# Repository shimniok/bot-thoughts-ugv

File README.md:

This is the repository of electronics and software for Data Bus and Troubled Child, my autonomous ground vehicles. 

* [Troubled Child](http://www.bot-thoughts.com/2014/06/avc-sharc-fsv.html) is a 1986 Jeep Grand Wagoneer that took 1st place in the 2014 Sparkfun AVC.
* [Data Bus](http://www.bot-thoughts.com/p/robot-mag-data-bus.html) is a 1:10 scale RC car that took 3rd place in the 2012 Sparkfun AVC.

The repository contains source code, schematics, board layouts, and documentation. Mostly this is a catch-all for what I worked on in 2010-2014.

* [Current Software](https://github.com/shimniok/diyrovers) - updated versions of the mbed software that handles pose estimation, navigation, and path following
* ```Software/``` - *older* mbed software that handles pose estimation, navigation, path following
* ```Documentation/``` - various supporting documents
* ```Hardware/``` - various hardware used in building and calibrating
* ```Electronics/``` - catch-all of circuit/layout designs varying from experiment to tried and tossed

Some of the electronics are now products on [Tindie.com](https://www.tindie.com/stores/bot_thoughts/) and they have their own repositories, shown below.

# Rover Products
* [RoverMux](https://github.com/shimniok/RoverMux) tried and true 3 channel R/C Multiplexer
* [RoverBaseboard](https://github.com/shimniok/RoverBaseboard) - a baseboard making it easy to hook up servos and sensors to an mbed/LPCXpresso
* [RoverGyro](https://github.com/shimniok/RoverGyro) - a breakout for low drift MAX21000 gyro (untested)
* [RoverPower](https://github.com/shimniok/RoverPower) - high current 5V power supply (untested)
* [RoverMeter](https://github.com/shimniok/RoverMeter) - I2C-based current monitor (untested)

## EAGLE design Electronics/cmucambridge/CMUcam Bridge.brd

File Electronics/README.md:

# Circuits for Sparkfun AVC Robot 2011

Various circuits for 2011 AVC ground robot

* 5vadcmbed/ - 5V-capable ADC for mbed
* Block Diagram.sch - block diagram for data bus
* cmucambridge/ - serial to I2C bridge for CMUcam (incomplete)
* duplexoptoiso/ - full duplex opto isolator, used during GPS experiments
* gfxlcd/ - graphic LCD
* microsdbreakout/ - maybe an old version of [eeZeeMicroSD](https://github.com/shimniok/eeZeeMicroSD)
* motherboard/ - original verion(s) of [RoverBaseboard](https://github.com/shimniok/RoverBaseboard)
* pdmodule/ - simple power distribution module 
* powersupply/ - power supply for MCU
* powersupply5/ - power supply for MCU
* rangeri2c/ - early version of analog-to-I2C module?
* rckillswitch/ - early version of [RoverMux](https://github.com/shimniok/RoverMux)
* seriali2cbridge/ - serial to I2C bridge, probably for AVRcam
* venusgps/ - Venus GPS mounting board(?)
* warningflasher/ - a warning flasher letting people know the vehicle is in autonomous mode
* wheelencoderadapter/ - an early version of [RoverEncoder](https://github.com/shimniok/RoverEncoder)

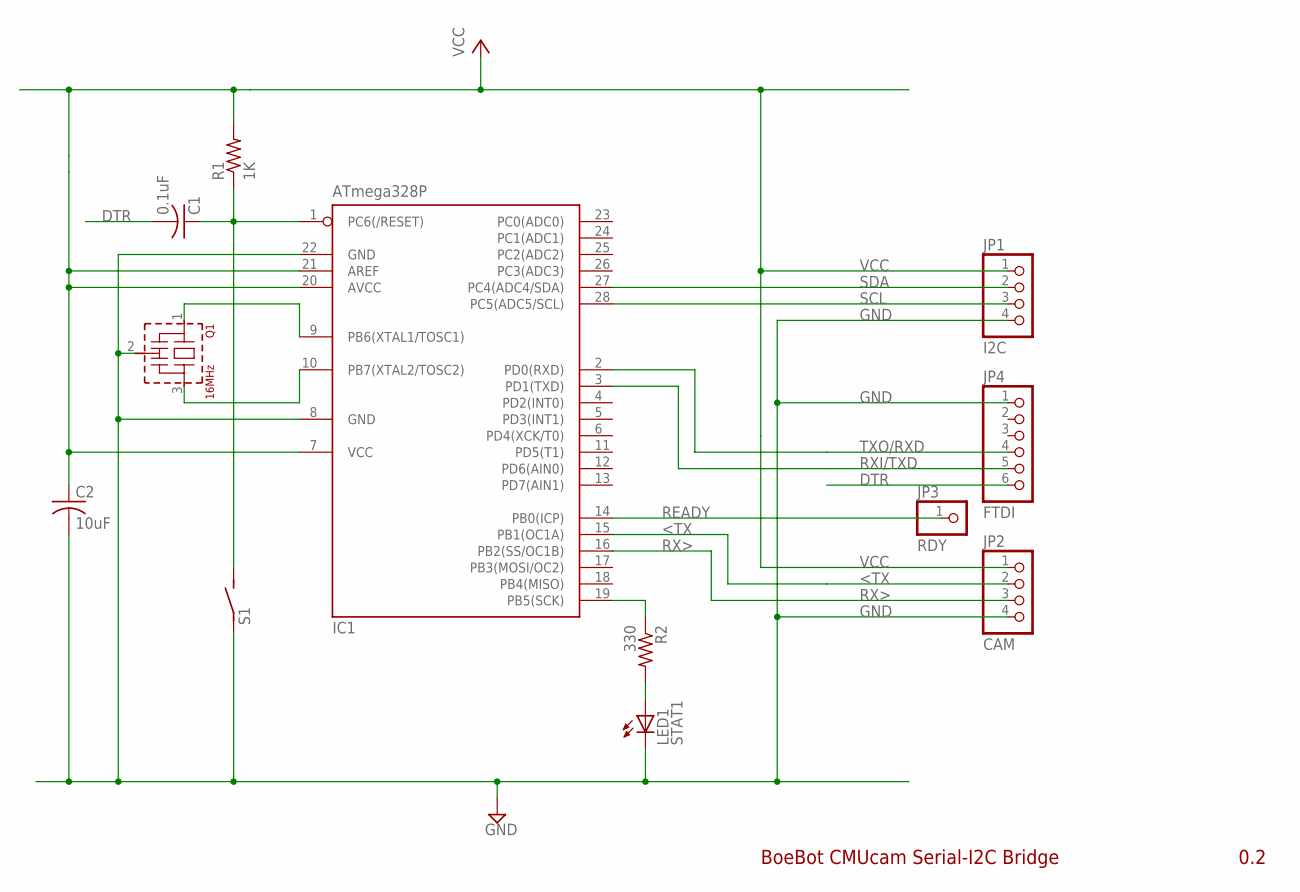
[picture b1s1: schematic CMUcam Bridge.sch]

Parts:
C1: 0.1uF; C0603; PARTNO CC0603ZRY5V7BB104
C2: 10uF; C0805; PARTNO C1608X5R0J105K
IC1: ATmega328P; DIL28-3; PARTNO DEV-10524
JP1: I2C; 1X04-S; PARTNO 2211S-04G
JP2: CAM; 1X04-S; PARTNO 2211S-04G
JP3: RDY; 1X01-S
JP4: FTDI; 1X06-S; PARTNO 2211S-06G
LED1: STAT1; LED3MM
Q1: 16MHz; CSTLS_G9; PARTNO AWCR-16.00MD
R1: 1K; 0204/7
R2: 330; R0603; PARTNO CRCW0603330RJNEA
S1: RESET\; EVQ11X09; PARTNO SALVAGE

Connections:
<TX: IC1.15 (PB1(OC1A)), JP2.2
DTR: C1.2, JP4.6
GND: C2.2, IC1.8 (GND), IC1.22 (GND), JP1.4, JP2.4, JP4.1, LED1.K (C), Q1.2 (VSS), S1.1
unnamed: IC1.9 (PB6(XTAL1/TOSC1)), Q1.1
unnamed: IC1.10 (PB7(XTAL2/TOSC2)), Q1.3
unnamed: LED1.A, R2.2
unnamed: IC1.19 (PB5(SCK)), R2.1
unnamed: C1.1, IC1.1 (PC6(/RESET)), R1.1, S1.2
READY: IC1.14 (PB0(ICP)), JP3.1
RX>: IC1.16 (PB2(SS/OC1B)), JP2.3
RXI/TXD: IC1.3 (PD1(TXD)), JP4.5
SCL: IC1.28 (PC5(ADC5/SCL)), JP1.3
SDA: IC1.27 (PC4(ADC4/SDA)), JP1.2
TXO/RXD: IC1.2 (PD0(RXD)), JP4.4
VCC: C2.1, IC1.7 (VCC), IC1.20 (AVCC), IC1.21 (AREF), JP1.1, JP2.1, R1.2

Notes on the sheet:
BoeBot CMUcam Serial-I2C Bridge
0.2

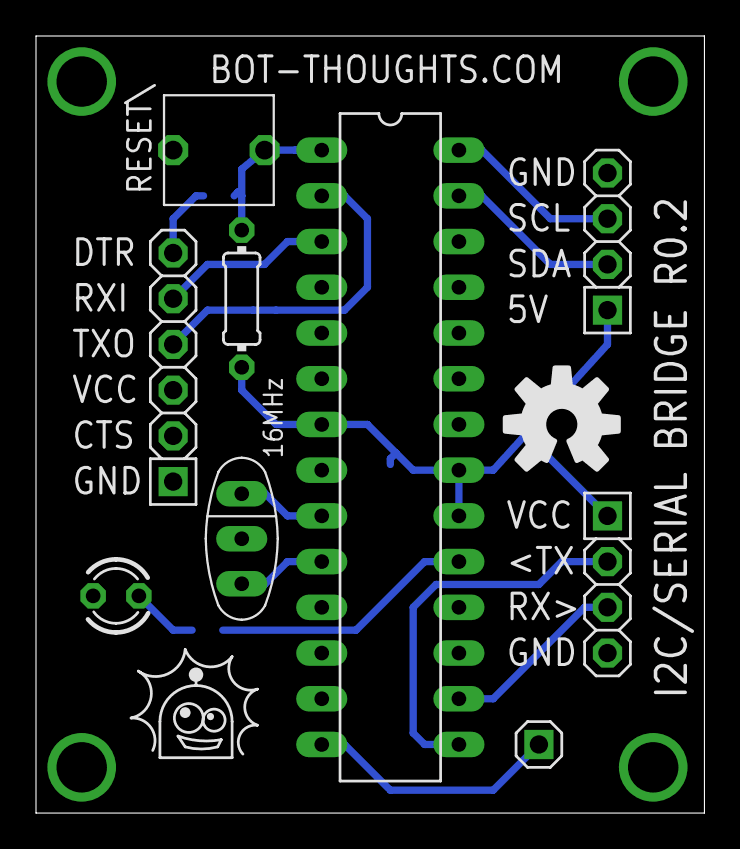
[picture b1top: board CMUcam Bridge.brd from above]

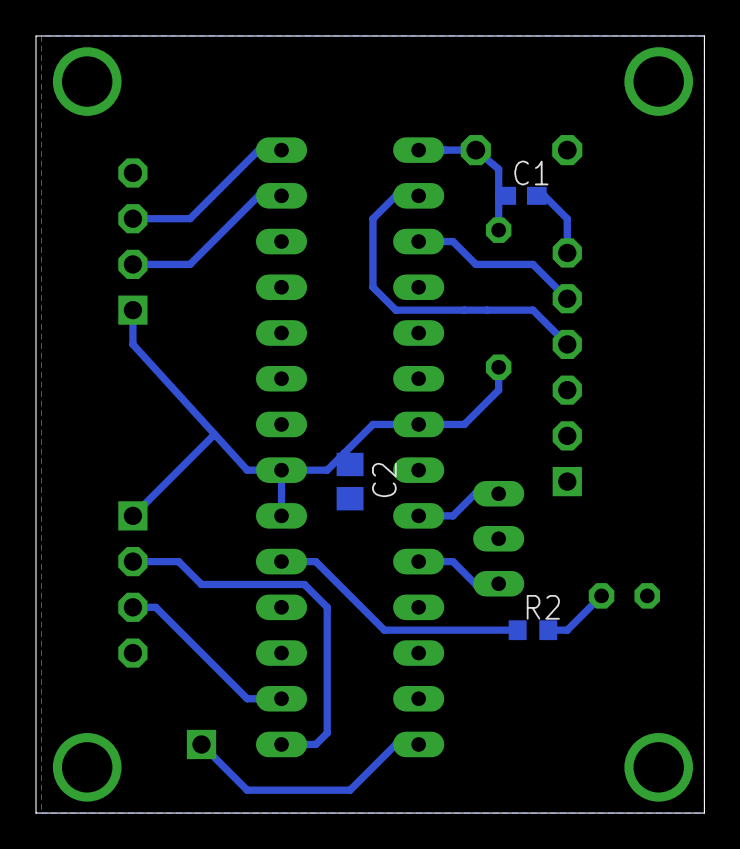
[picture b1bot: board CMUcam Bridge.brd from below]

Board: 2 copper layers, 37.1 x 43.2 mm, 12 parts (3 on the bottom side), 15 nets.

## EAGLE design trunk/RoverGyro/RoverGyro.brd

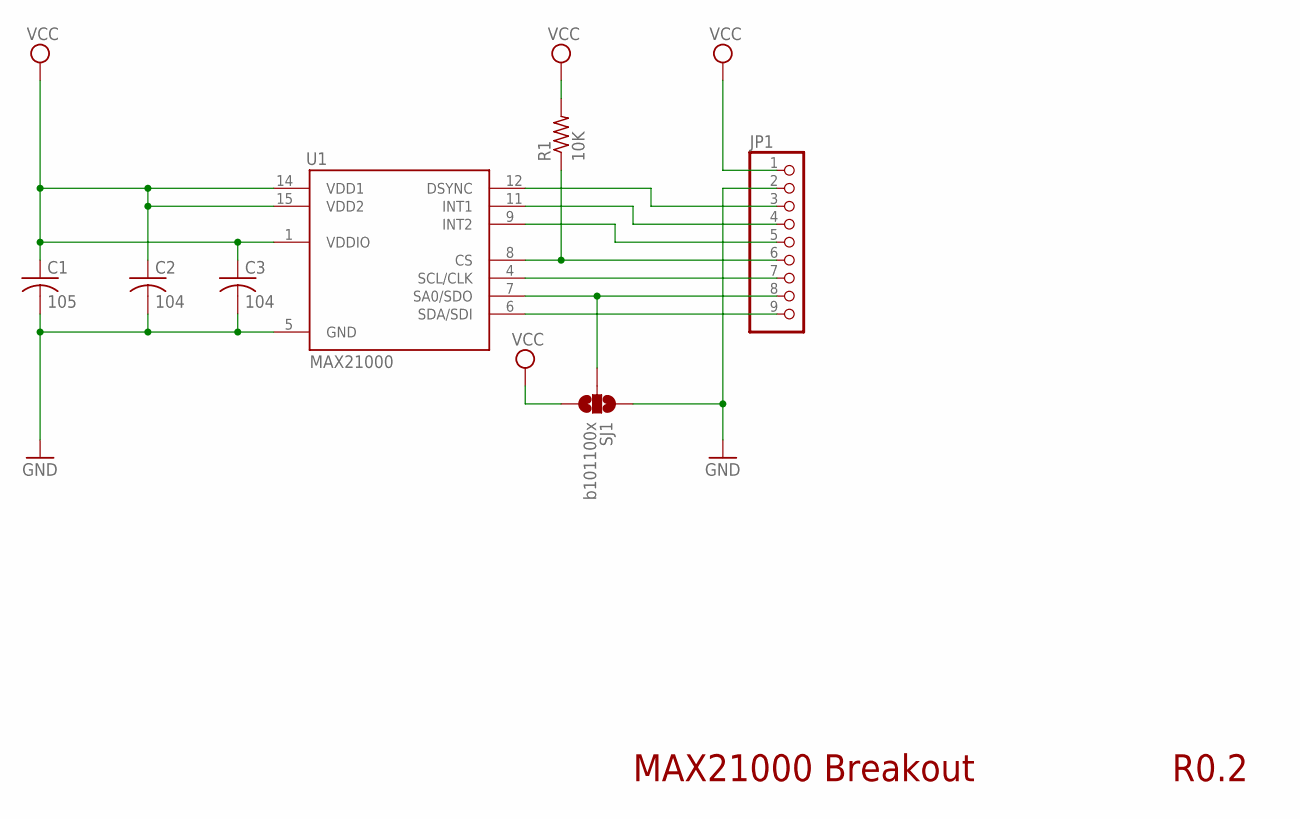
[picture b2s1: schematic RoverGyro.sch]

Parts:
C1: 105; C0603
C2, C3: 104; C0603
JP1: PINHD-1X09_2.54-S; 1X09-S
R1: 10K; R0603
SJ1: b101100x; SJ_3
U1: MAX21000; 16LGA

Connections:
CS: JP1.6, R1.1, U1.8 (CS)
DSYNC: JP1.3, U1.12 (DSYNC)
GND: C1.2, C2.2, C3.2, JP1.2, SJ1.1, U1.5 (GND)
INT1: JP1.4, U1.11 (INT1)
INT2: JP1.5, U1.9 (INT2)
SA0/SDO: JP1.8, SJ1.2, U1.7 (SA0/SDO)
SCL/SCK: JP1.7, U1.4 (SCL/CLK)
SDA/SDI: JP1.9, U1.6 (SDA/SDI)
VCC: C1.1, C2.1, C3.1, JP1.1, R1.2, SJ1.3, U1.1 (VDDIO), U1.14 (VDD1), U1.15 (VDD2)

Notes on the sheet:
MAX21000 Breakout
R0.2

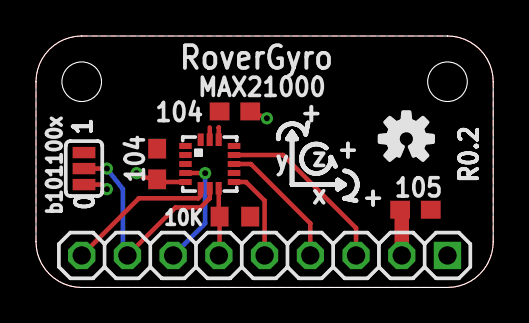
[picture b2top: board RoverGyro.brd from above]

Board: 2 copper layers, 25.4 x 14.0 mm, 8 parts (0 on the bottom side), 9 nets.

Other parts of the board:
U$1: OSHW-LOGO-S

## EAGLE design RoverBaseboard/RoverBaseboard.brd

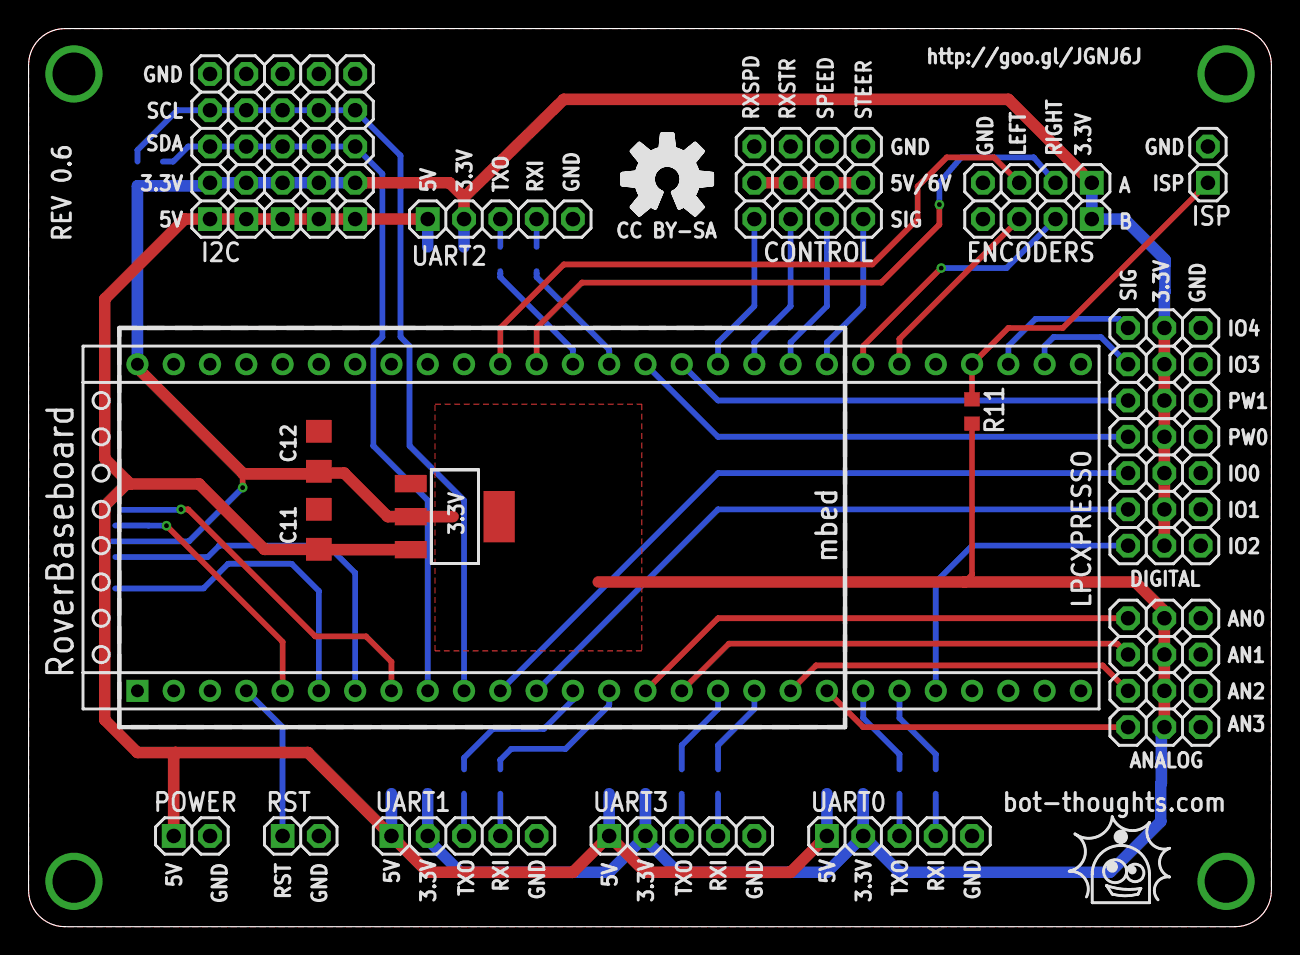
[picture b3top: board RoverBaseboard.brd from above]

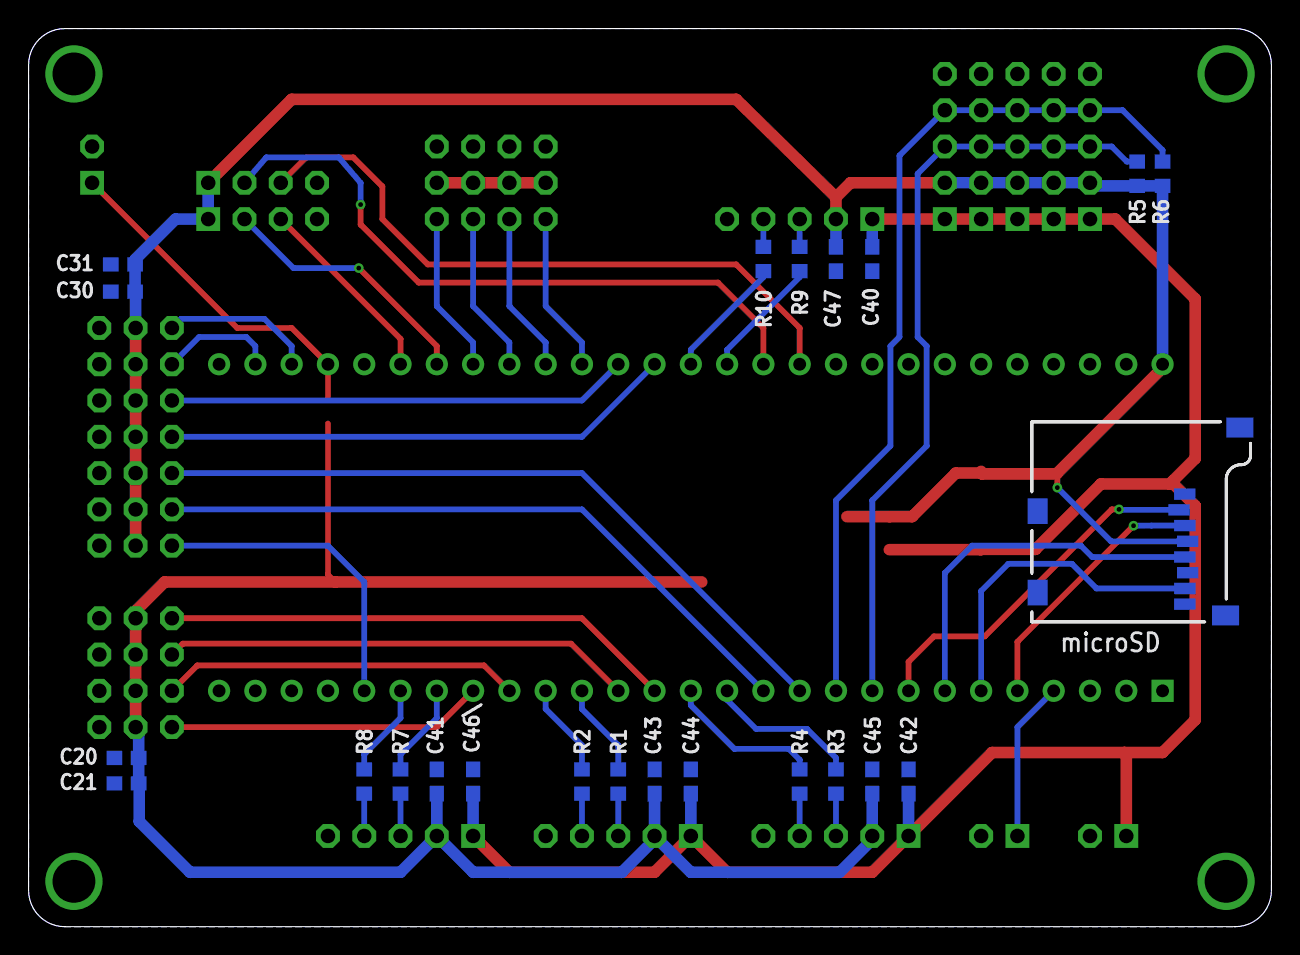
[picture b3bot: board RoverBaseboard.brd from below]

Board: 2 copper layers, 87.0 x 62.9 mm, 57 parts (23 on the bottom side), 47 nets.

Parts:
C11, C12: 10uF; C1206
C20, C30, C40, C41, C42, C43, C44, C45, C46\, C47: 106; C0603
C21, C31: 104; C0603
IC3: 3.3V; SOT223
JP1: D0; 1X03-S
JP2: B; 1X04-S
JP3: POWER; 1X02-S
JP4: RST; 1X02-S
JP5: RXSPD; 1X03-S
JP6: RXSTR; 1X03-S
JP7: UART0; 1X05-S
JP8: SPEED; 1X03-S
JP9: STEER; 1X03-S
JP10: P1; 1X03-S
JP11: P2; 1X03-S
JP13: D1; 1X03-S
JP14: D2; 1X03-S
JP15: A; 1X04-S
JP16: A0; 1X03-S
JP17: A1; 1X03-S
JP18: A2; 1X03-S
JP19: A3; 1X03-S
JP20: UART1; 1X05-S
JP21: UART2; 1X05-S
JP22: UART3; 1X05-S
JP23: I2C; 1X05-S
JP24, JP25, JP26, JP27: 1X05-S
JP28: D7; 1X03-S
JP29: D8; 1X03-S
JP30: ISP; 1X02-S
R1, R2, R3, R4, R7, R8, R9, R10, R11: 10K; R0603
R5, R6: 2.2K; R0603
U2: microSD; MICRO-SD-SOCKET-PP
U$1: LPCXPRESSO; LPCXPRESSO_NO_PAD

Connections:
!CS1: U2.2, U$1.J6-8
!ISP: JP30.1, R11.1, U$1.J6-51
!RESET: JP4.1, U$1.J6-4
+3V3: C12.1, C20.1, C21.1, C30.1, C31.1, C41.1, C43.1, C45.1, C47.1, IC3.2, IC3.4, JP1.2, JP2.1, JP7.2, JP10.2, JP11.2, JP13.2, JP14.2, JP15.1, JP16.2, JP17.2, JP18.2, JP19.2, JP20.2, JP21.2, JP22.2, JP23.2, JP24.2, JP25.2, JP26.2, JP27.2, JP28.2, JP29.2, R5.2, R6.2, R11.2, U2.4, U$1.J6-28
+5V: C11.1, C40.1, C42.1, C44.1, C46\.1, IC3.3, JP3.1, JP7.1, JP20.1, JP21.1, JP22.1, JP23.1, JP24.1, JP25.1, JP26.1, JP27.1
A0: JP16.1, U$1.J6-15
A1: JP17.1, U$1.J6-16
A2: JP18.1, U$1.J6-19
A3: JP19.1, U$1.J6-20
BEC: JP5.2, JP6.2, JP8.2, JP9.2
D2: JP14.1, U$1.J6-23
D7: JP28.1, U$1.J6-53
D8: JP29.1, U$1.J6-52
ENCA_LEFT: JP15.3, U$1.J6-38
ENCA_RIGHT: JP15.2, U$1.J6-39
ENCB_LEFT: JP2.3, U$1.J6-49
ENCB_RIGHT: JP2.2, U$1.J6-48
GND: C11.2, C12.2, C20.2, C21.2, C30.2, C31.2, C40.2, C41.2, C42.2, C43.2, C44.2, C45.2, C46\.2, C47.2, IC3.1, JP1.3, JP2.4, JP3.2, JP4.2, JP5.3, JP6.3, JP7.5, JP8.3, JP9.3, JP10.3, JP11.3, JP13.3, JP14.3, JP15.4, JP16.3, JP17.3, JP18.3, JP19.3, JP20.5, JP21.5, JP22.5, JP23.5, JP24.5, JP25.5, JP26.5, JP27.5, JP28.3, JP29.3, JP30.2, U2.6, U2.GND1, U2.GND3, U$1.J6-1, U$1.J6-54
MISO1: U2.7, U$1.J6-6
MOSI1: U2.3, U$1.J6-5
unnamed: JP22.3, R1.2
unnamed: JP22.4, R2.2
unnamed: JP7.3, R7.2
unnamed: JP7.4, R8.2
unnamed: JP20.3, R3.2
unnamed: JP20.4, R4.2
unnamed: JP21.3, R9.2
unnamed: JP21.4, R10.2
P11: JP1.1, U$1.J6-11
P12: JP13.1, U$1.J6-12
PWM1: JP10.1, U$1.J6-42
PWM2: JP11.1, U$1.J6-43
RXD0: R8.1, U$1.J6-22
RXD1: R4.1, U$1.J6-14
RXD2: R10.1, U$1.J6-41
RXD3: R2.1, U$1.J6-18
RXSPD: JP5.1, U$1.J6-44
RXSTR: JP6.1, U$1.J6-45
SCK1: U2.5, U$1.J6-7
SCL: JP23.4, JP24.4, JP25.4, JP26.4, JP27.4, R6.1, U$1.J6-10
SDA: JP23.3, JP24.3, JP25.3, JP26.3, JP27.3, R5.1, U$1.J6-9
SPEED: JP8.1, U$1.J6-46
STEER: JP9.1, U$1.J6-47
TXD0: R7.1, U$1.J6-21
TXD1: R3.1, U$1.J6-13
TXD2: R9.1, U$1.J6-40
TXD3: R1.1, U$1.J6-17

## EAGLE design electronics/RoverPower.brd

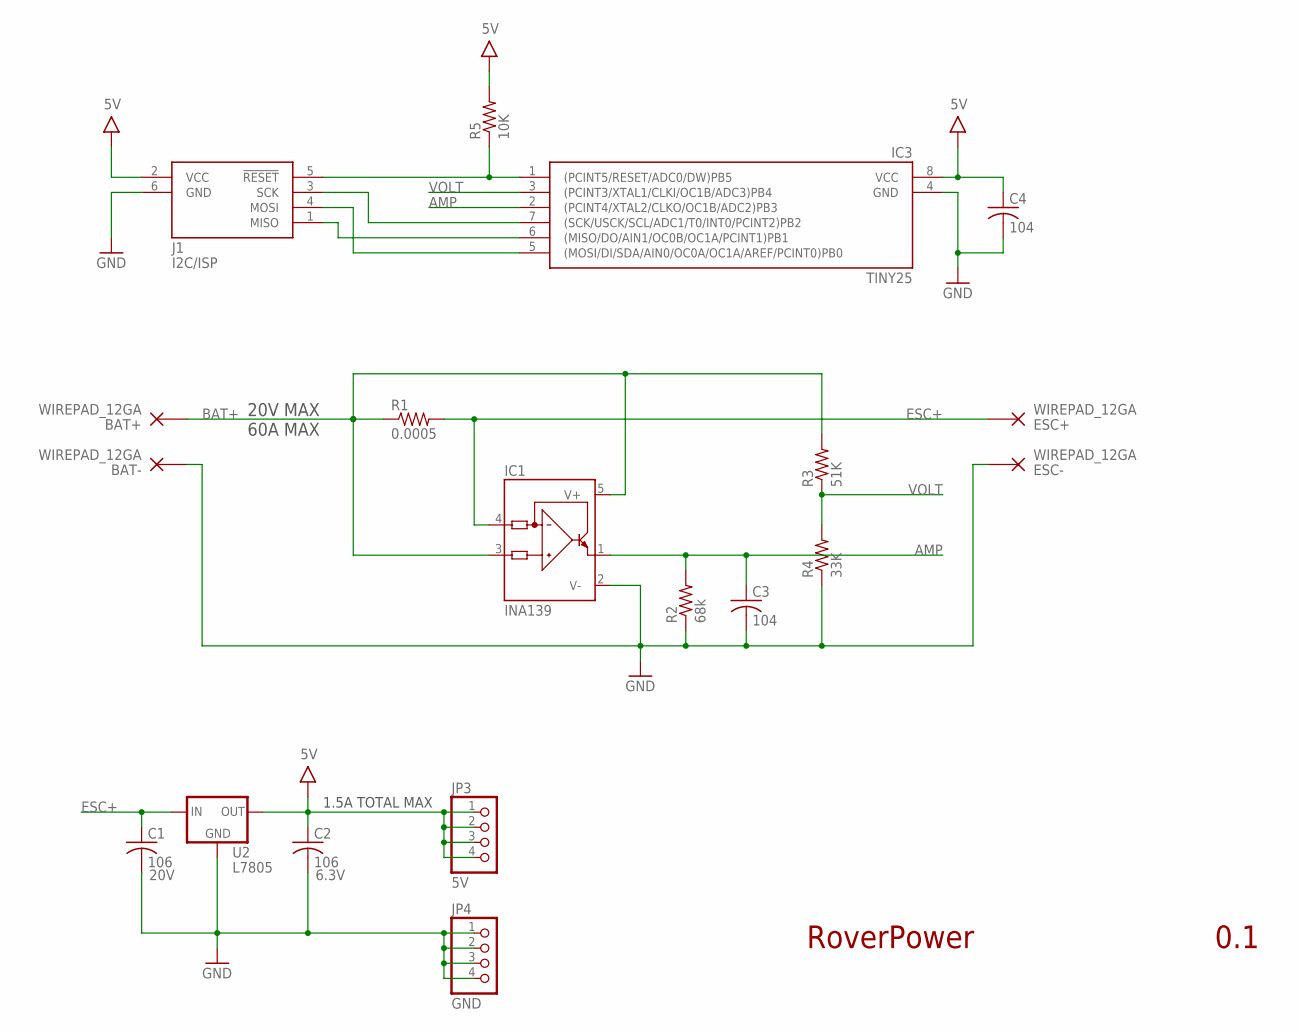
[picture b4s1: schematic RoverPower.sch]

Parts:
BAT+: WIREPAD_12GA; PAD_12GA
BAT-: WIREPAD_12GA; PAD_12GA
C1: 106; C1206; VOLTAGE 20V
C2: 106; C1206; VOLTAGE 6.3V
C3, C4: 104; C0603
ESC+: WIREPAD_12GA; PAD_12GA
ESC-: WIREPAD_12GA; PAD_12GA
IC1: INA139; SOT23-5
IC3: TINY25; SOIC8
J1: I2C/ISP; CON6P2R
JP3: 5V; 1X04-S
JP4: GND; 1X04-S
R1: 0.0005; R2512
R2: 68k; R0603
R3: 51K; R0603
R4: 33K; R0603
R5: 10K; R0603
U2: L7805; D2PAK

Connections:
5V: C2.1, C4.1, IC3.8 (VCC), J1.2 (VCC), JP3.1, JP3.2, JP3.3, JP3.4, R5.2, U2.3 (OUT)
!RESET: IC3.1 ((PCINT5/RESET/ADC0/DW)PB5), J1.5 (!RESET), R5.1
AMP: C3.1, IC1.1 (OUT), IC3.2 ((PCINT4/XTAL2/CLKO/OC1B/ADC2)PB3), R2.2
BAT+: BAT+.P$1, IC1.3 (IN+), IC1.5 (V+), R1.P$1 (1), R3.2
ESC+: C1.1, ESC+.P$1, IC1.4 (IN-), R1.P$2 (2), U2.1 (IN)
GND: BAT-.P$1, C1.2, C2.2, C3.2, C4.2, ESC-.P$1, IC1.2 (V-), IC3.4 (GND), J1.6 (GND), JP4.1, JP4.2, JP4.3, JP4.4, R2.1, R4.1, U2.2 (GND)
MISO: IC3.6 ((MISO/DO/AIN1/OC0B/OC1A/PCINT1)PB1), J1.1 (MISO)
SCL: IC3.7 ((SCK/USCK/SCL/ADC1/T0/INT0/PCINT2)PB2), J1.3 (SCK)
SDA: IC3.5 ((MOSI/DI/SDA/AIN0/OC0A/OC1A/AREF/PCINT0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), J1.4 (MOSI)
VOLT: IC3.3 ((PCINT3/XTAL1/CLKI/OC1B/ADC3)PB4), R3.1, R4.2

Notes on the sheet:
RoverPower
0.1
20V MAX
60A MAX
1.5A TOTAL MAX

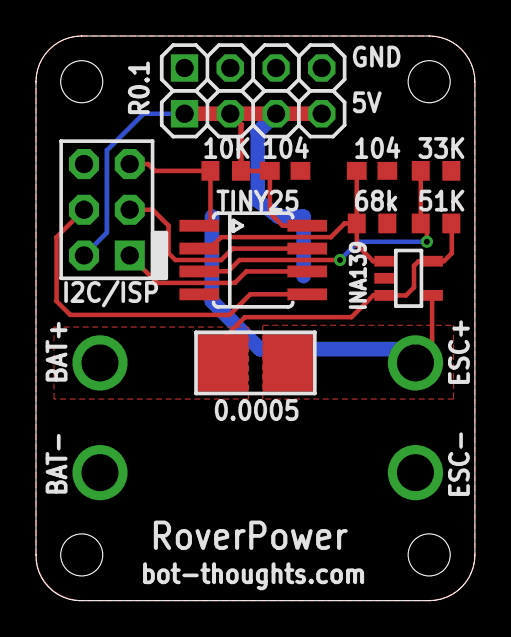
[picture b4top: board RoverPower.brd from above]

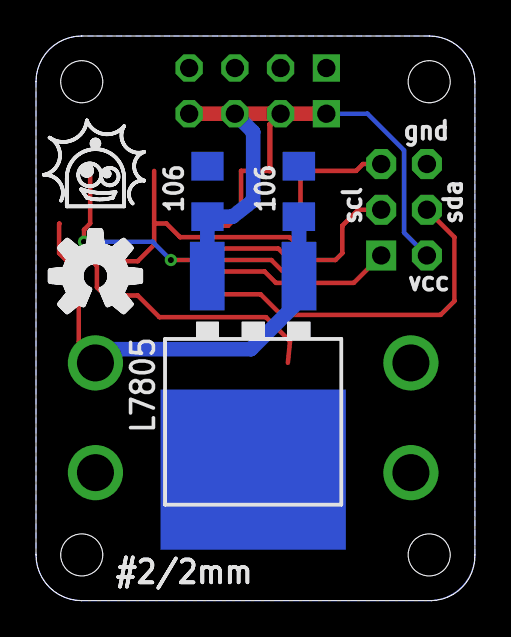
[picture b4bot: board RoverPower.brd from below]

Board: 2 copper layers, 24.4 x 31.4 mm, 19 parts (3 on the bottom side), 10 nets.

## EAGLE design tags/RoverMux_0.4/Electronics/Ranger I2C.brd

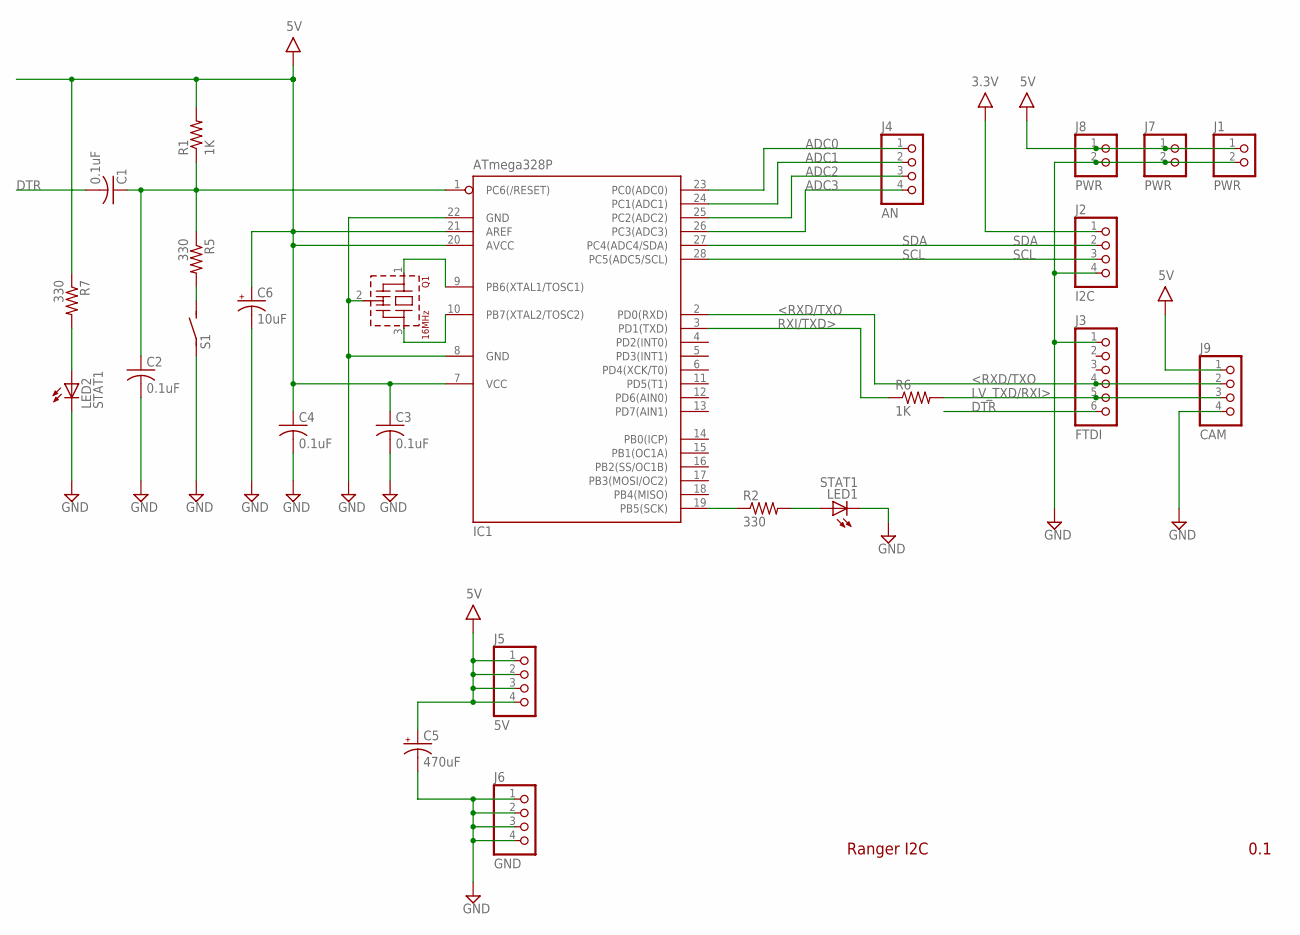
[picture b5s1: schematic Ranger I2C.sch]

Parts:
C1: 0.1uF; C050-024X044; PARTNO CC0603ZRY5V7BB104
C2, C3, C4: 0.1uF; C050-024X044; PARTNO C1608X5R0J105K
C5: 470uF; E2,5-6
C6: 10uF; E2,5-6
IC1: ATmega328P; DIL28-3; PARTNO DEV-10524
J1, J7, J8: PWR; 1X02-S
J2: I2C; 1X04-S; PARTNO 2211S-04G
J3: FTDI; 1X06-S; PARTNO 2211S-06G
J4: AN; 1X04-S; PARTNO 2211S-04G
J5: 5V; 1X04-S; PARTNO 2211S-04G
J6: GND; 1X04-S; PARTNO 2211S-04G
J9: CAM; 1X04-S; PARTNO 2211S-04G
LED1, LED2: STAT1; LED3MM
Q1: 16MHz; CSTLS_G9; PARTNO AWCR-16.00MD
R1: 1K; 0204/5
R2, R5, R7: 330; 0204/5; PARTNO CRCW0603330RJNEA
R6: 1K; 0204/5; PARTNO CRCW0603330RJNEA
S1: RESET\; EVQ11X09; PARTNO SALVAGE

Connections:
3.3V: J2.1
5V: C3.1, C4.1, C5.+, C6.+, IC1.7 (VCC), IC1.20 (AVCC), IC1.21 (AREF), J1.1, J5.1, J5.2, J5.3, J5.4, J7.1, J8.1, J9.1, R1.2, R7.1
<RXD/TXO: IC1.2 (PD0(RXD)), J3.4, J9.2
ADC0: IC1.23 (PC0(ADC0)), J4.1
ADC1: IC1.24 (PC1(ADC1)), J4.2
ADC2: IC1.25 (PC2(ADC2)), J4.3
ADC3: IC1.26 (PC3(ADC3)), J4.4
DTR: C1.2, J3.6
GND: C2.2, C3.2, C4.2, C5.-, C6.-, IC1.8 (GND), IC1.22 (GND), J1.2, J2.4, J3.1, J6.1, J6.2, J6.3, J6.4, J7.2, J8.2, J9.4, LED1.K (C), LED2.K (C), Q1.2 (VSS), S1.1
LV_TXD/RXI>: J3.5, J9.3, R6.2
unnamed: IC1.9 (PB6(XTAL1/TOSC1)), Q1.1
unnamed: IC1.10 (PB7(XTAL2/TOSC2)), Q1.3
unnamed: LED1.A, R2.2
unnamed: IC1.19 (PB5(SCK)), R2.1
unnamed: C1.1, C2.1, IC1.1 (PC6(/RESET)), R1.1, R5.1
unnamed: R5.2, S1.2
unnamed: LED2.A, R7.2
RXI/TXD>: IC1.3 (PD1(TXD)), R6.1
SCL: IC1.28 (PC5(ADC5/SCL)), J2.3
SDA: IC1.27 (PC4(ADC4/SDA)), J2.2

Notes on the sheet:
Ranger I2C
0.1

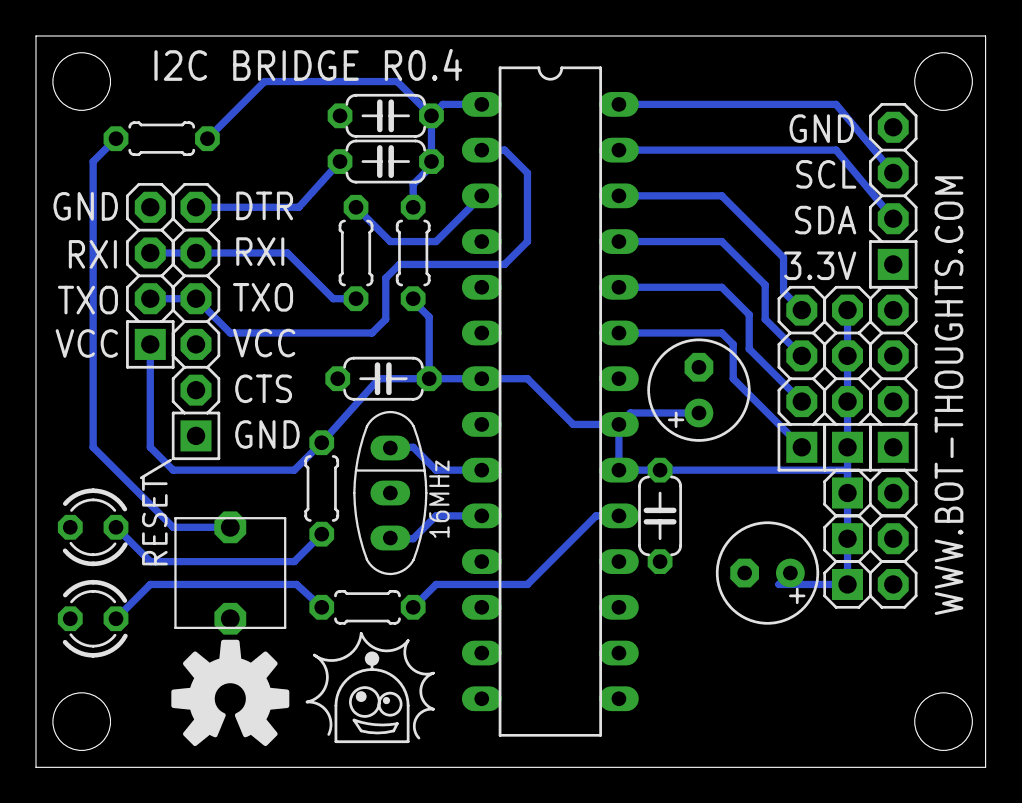
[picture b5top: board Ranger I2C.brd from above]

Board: 2 copper layers, 52.8 x 40.6 mm, 25 parts (0 on the bottom side), 19 nets.

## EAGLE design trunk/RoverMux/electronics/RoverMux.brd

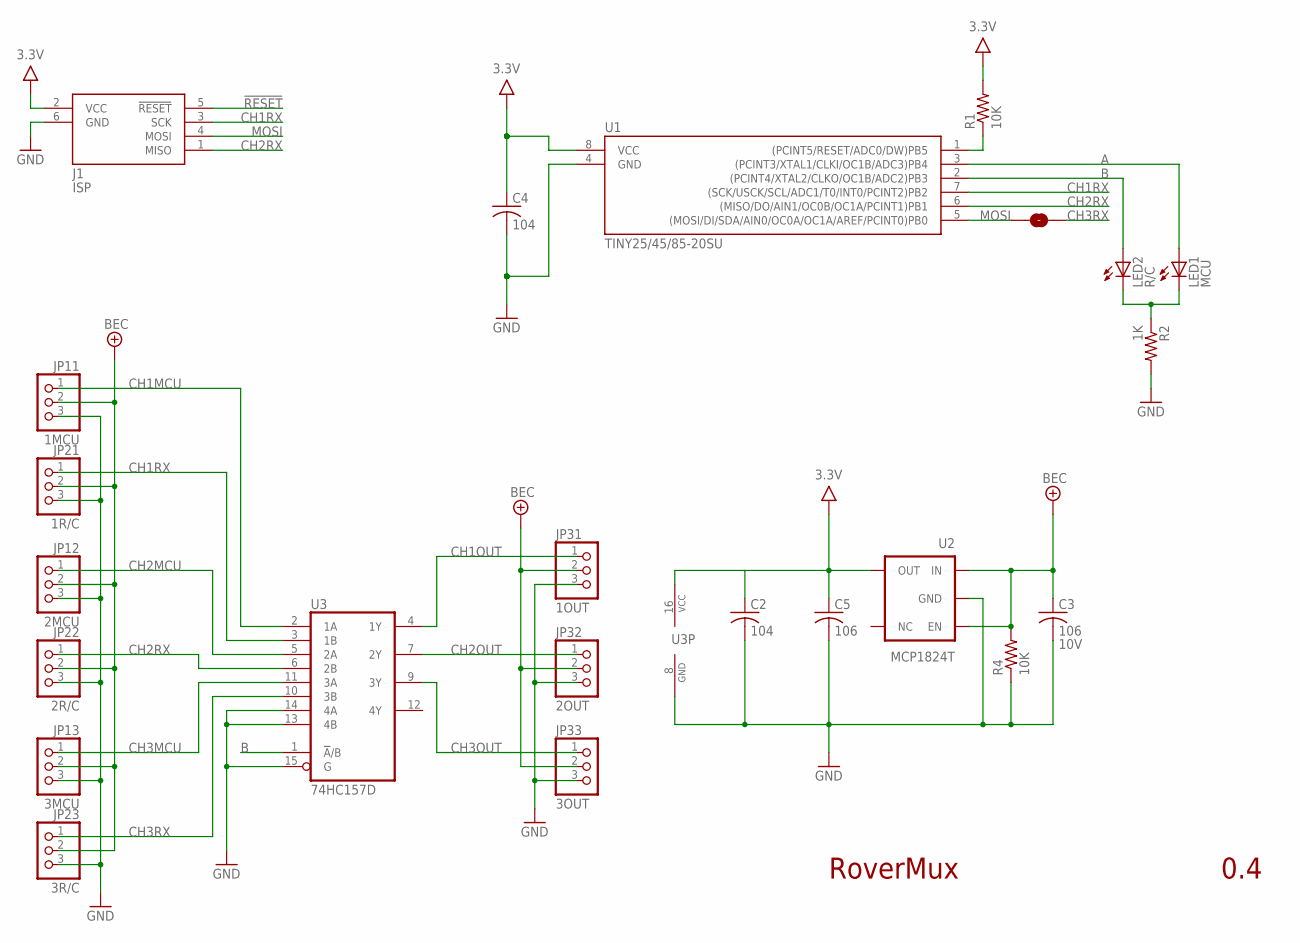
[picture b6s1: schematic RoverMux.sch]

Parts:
C2, C4: 104; C0603; PARTNO C1608X7R1E104K080AA
C3: 106; C0603; VOLTAGE 10V; PARTNO CL10A106MP8NNNC
C5: 106; C0603; PARTNO CL10A106MP8NNNC
J1: ISP; CON6P2R
JP11: 1MCU; 1X03-S
JP12: 2MCU; 1X03-S
JP13: 3MCU; 1X03-S
JP21: 1R/C; 1X03-S
JP22: 2R/C; 1X03-S
JP23: 3R/C; 1X03-S
JP31: 1OUT; 1X03-S
JP32: 2OUT; 1X03-S
JP33: 3OUT; 1X03-S
LED1: MCU; CHIPLED_1206; PARTNO LH N974-KN-1
LED2: R/C; CHIPLED_1206; PARTNO LG N971-KN-1
R1, R4: 10K; R0603; PARTNO 1622829-1
R2: 1K; R0603; PARTNO RC0603JR-07330RL
SJ1: CH3; SJ_2S-NOTRACE
U1: TINY25/45/85-20SU; SOIC8
U2: MCP1824T; SOT23-5; PARTNO MCP1824T-5002E/OT
U3: 74HC157D; SO16; PARTNO 74HCT157D,652

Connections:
3.3V: C2.1, C4.1, C5.1, J1.2 (VCC), R1.2, U1.8 (VCC), U2.5 (OUT), U3.16 (VCC)
!RESET: J1.5 (!RESET), R1.1, U1.1 ((PCINT5/RESET/ADC0/DW)PB5)
A: LED1.A, U1.3 ((PCINT3/XTAL1/CLKI/OC1B/ADC3)PB4)
B: LED2.A, U1.2 ((PCINT4/XTAL2/CLKO/OC1B/ADC2)PB3), U3.1 (!A!/B)
BEC: C3.1, JP11.2, JP12.2, JP13.2, JP21.2, JP22.2, JP23.2, JP31.2, JP32.2, JP33.2, R4.2, U2.1 (IN), U2.3 (EN)
CH1MCU: JP11.1, U3.2 (1A)
CH1OUT: JP31.1, U3.4 (1Y)
CH1RX: J1.3 (SCK), JP21.1, U1.7 ((SCK/USCK/SCL/ADC1/T0/INT0/PCINT2)PB2), U3.3 (1B)
CH2MCU: JP12.1, U3.5 (2A)
CH2OUT: JP32.1, U3.7 (2Y)
CH2RX: J1.1 (MISO), JP22.1, U1.6 ((MISO/DO/AIN1/OC0B/OC1A/PCINT1)PB1), U3.6 (2B)
CH3MCU: JP13.1, U3.11 (3A)
CH3OUT: JP33.1, U3.9 (3Y)
CH3RX: JP23.1, SJ1.2, U3.10 (3B)
GND: C2.2, C3.2, C4.2, C5.2, J1.6 (GND), JP11.3, JP12.3, JP13.3, JP21.3, JP22.3, JP23.3, JP31.3, JP32.3, JP33.3, R2.2, R4.1, U1.4 (GND), U2.2 (GND), U3.8 (GND), U3.13 (4B), U3.14 (4A), U3.15 (G)
MOSI: J1.4 (MOSI), SJ1.1, U1.5 ((MOSI/DI/SDA/AIN0/OC0A/OC1A/AREF/PCINT0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)
unnamed: LED1.C, LED2.C, R2.1

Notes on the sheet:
RoverMux
0.4

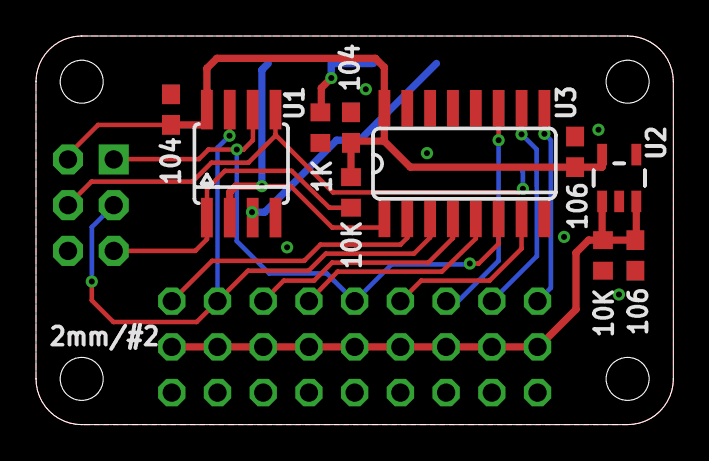
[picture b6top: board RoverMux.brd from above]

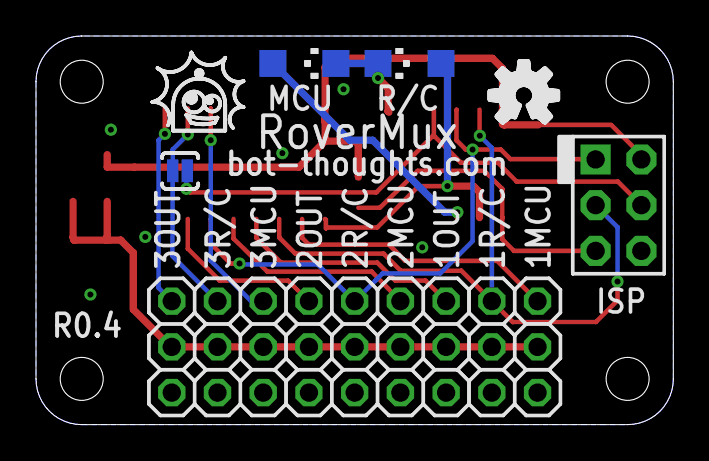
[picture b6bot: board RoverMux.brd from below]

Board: 2 copper layers, 35.4 x 21.6 mm, 23 parts (13 on the bottom side), 17 nets.

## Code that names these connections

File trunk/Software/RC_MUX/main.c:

/*
 * main.c
 *
 * This firmware runs an RC multiplexer that switches between autonomous and manual control of a robot.
 * A timeout value is subtracted every ~10us. If an RC signal is present, this timeout is reset and Manual
 * Mode is selected. When no RC signal is present for the duration of the timeout period, Autonomous Mode
 * is selected.
 *
 *  Created on: Jul 12, 2013
 *      Author: mes
 */

#include <avr/io.h>
#include <avr/interrupt.h>
#include <util/delay.h>

/*************** DEFINITIONS ****************/

#define CH1RX		PB2
#define CH1INT		PCINT2
#define CH3RX		PB0
#define CH3INT		PCINT0

#define MINPERIOD	5000L
#define MAXPERIOD	50000L
#define MINONTIME	300L
#define MAXONTIME	3000L

#define	TRUE		1
#define FALSE		0

#define MCUenable	PB3
#define RCenable	PB4
#define AUTO		1
#define MANUAL		0

#define VALIDCNT	3				// number of valid signals required to go manual
#define DT			100				// delta time for ticks, usec
#define TIMEOUT		60000L			// timeout in microseconds

/************* GLOBAL VARIABLES **************/

volatile uint8_t mode=AUTO;			// Mode of operation, auto or manual

volatile uint8_t inactive1=VALIDCNT;// RX signal active pulse counter
volatile long ontime1;  			// measure length of signal on time
volatile long offtime1; 			// measure length of signal off time

volatile uint8_t inactive3=VALIDCNT;// RX signal valid counter
volatile long ontime3;  			// measure length of signal on time
volatile long offtime3; 			// measure length of signal off time

/****************** CODE *********************/

int main() {
	/* setup pins for output */
	DDRB = (1<<MCUenable)|(1<<RCenable);

	/* Setup timer to keep track of timing of signal */
	TCCR0A = (1<<WGM01);					// CTC mode
	TCCR0B = (0<<CS02)|(1<<CS01)|(0<<CS00); // clk/8, 9.6MHz -> 1.2MHz
	OCR0A = 111; 							// 1.2MHz / 120 -> 10kHz, 100usec
	TIMSK0 = (1<<OCIE0A);					// Enable output compare A interrupt

	/* Setup pin interrupts for input signals */
	PCMSK |= (1<<CH1INT)|(1<<CH3INT);	// Enable interrupt for PB1/PCINT1
	GIMSK |= (1<<PCIE);					// Enable pin change interrupts

	/* Ready to receive interrupts, now */
	sei();

	while (1);
}


/**
 * Interupt handler for pin change, detects and tracks RC signal
 */
ISR(PCINT0_vect) {
	long p;
	// Check ontime, period on rising edge
	if ((PINB & (1<<CH1RX)) != 0) {
		// If signal period is around 20ms and on-period is ~1-2ms, we have a valid signal
		p = ontime1+offtime1;
		if (inactive1 && p > MINPERIOD && p < MAXPERIOD && ontime1 > MINONTIME && ontime1 < MAXONTIME) {
			--inactive1;
		}
		ontime1 = offtime1 = 0;
	}

	if ((PINB & (1<<CH3RX)) != 0) {
		p = ontime3+offtime3;
		if (inactive3 && p > MINPERIOD && p < MAXPERIOD && ontime3 > MINONTIME && ontime3 < MAXONTIME) {
			--inactive3;
		}
		ontime3 = offtime3 = 0;
	}

	if (!inactive3) {
		if (ontime3 > 1500) {
			PORTB = (1<<RCenable);
		} else {
			PORTB = (1<<MCUenable);
		}
	} else if (!inactive1) {
		PORTB = (1<<RCenable);
	}

}


/**
 * Timer interrupt handler, fires every ~10us and subtracts from timeout value
 */
ISR(TIM0_COMPA_vect) {
	if ((PINB & (1<<CH1RX)) == 0) {
		offtime1 += DT;  // track off time
		if (offtime1 > TIMEOUT) {
			inactive1 = VALIDCNT;
			ontime1 = offtime1 = 0;
		}
	} else {
		ontime1 += DT;   // track on time
	}

	if ((PINB & (1<<CH3RX)) == 0) {
		offtime3 += DT;  // track off time
		if (offtime3 > TIMEOUT) {
			inactive3 = VALIDCNT;
			ontime3 = offtime1 = 0;
		}
	} else {
		ontime3 += DT;   // track on time
	}

	if (inactive1 && inactive3) {
		PORTB = (1<<MCUenable);
	}
}

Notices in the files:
RoverBaseboard/RoverBaseboard.brd:
CC BY-SA
parts and their libraries:
SparkFun: Licensing: CC v3.0 Share-Alike You are welcome to use this library for commercial purposes.
